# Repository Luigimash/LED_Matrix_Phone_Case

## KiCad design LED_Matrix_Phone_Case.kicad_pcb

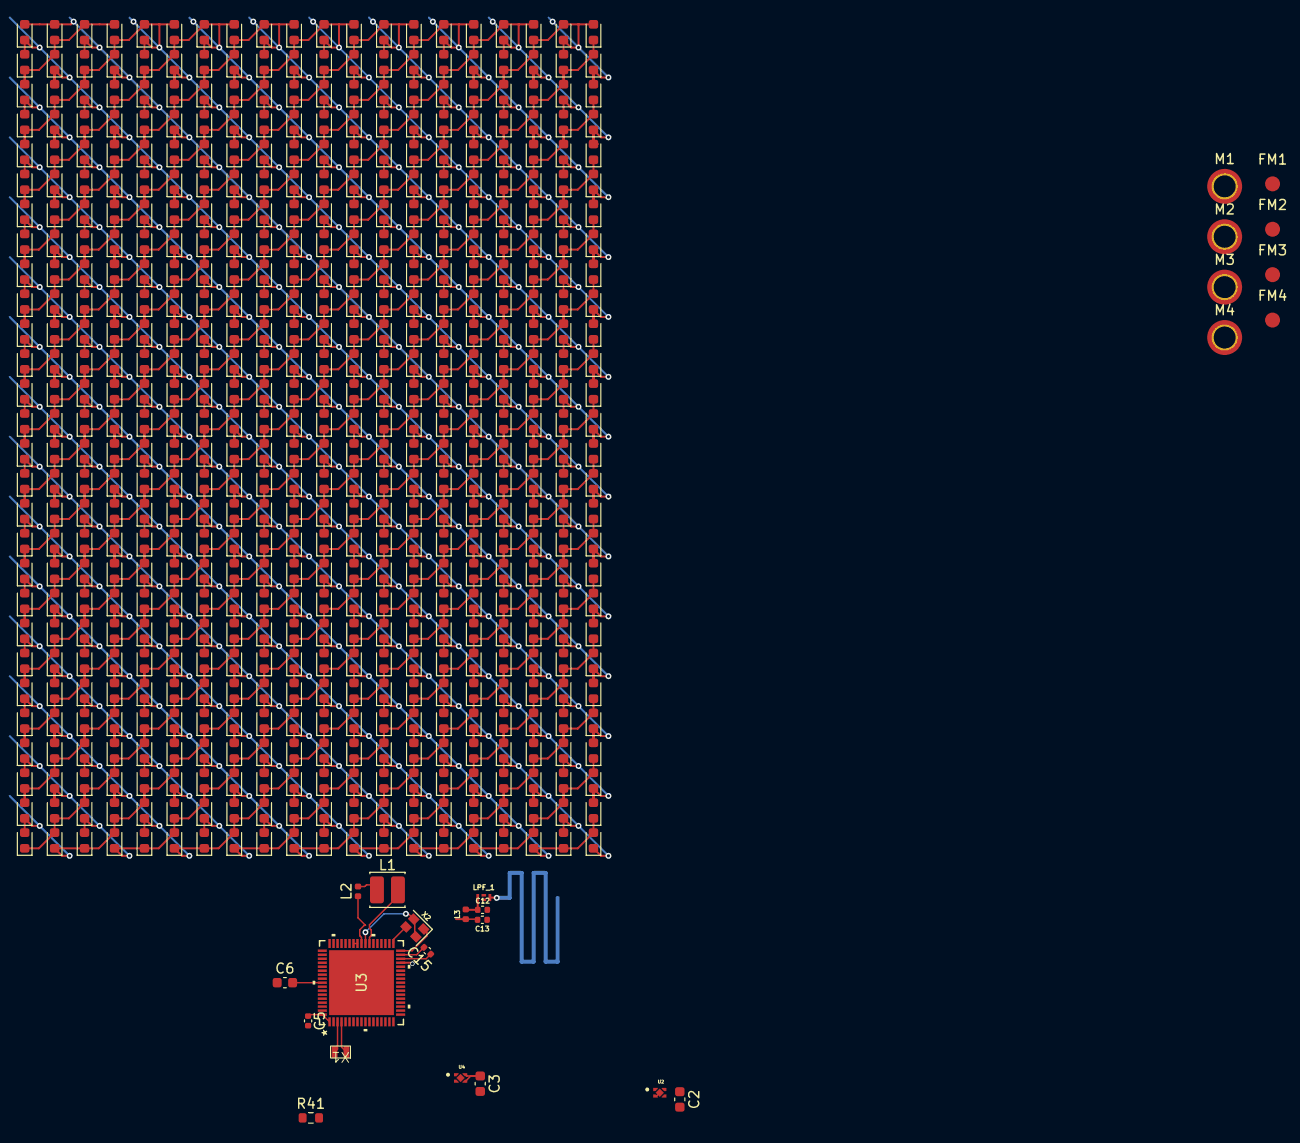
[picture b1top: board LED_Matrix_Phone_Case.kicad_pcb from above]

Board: 2 copper layers, 25 parts (0 on the bottom side), 14 nets.

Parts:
C2, C3: 4.7uF; C_0603_1608Metric
C5, C15: 100nF; C_0402_1005Metric
C6: 4.7µF; C_0603_1608Metric
C12: 0.3pF; C_0402_1005Metric
C13: 0.8pF; C_0402_1005Metric
FM1, FM2, FM3, FM4: Fiducial; Fiducial_1.5mm_Mask3mm
L1: 10uH; L_Cenker_CKCS3015
L2: 10nH; L_0402_1005Metric
L3: 2.7nH; L_0402_1005Metric
LPF_1: DLF162500LT-5028A1 - Low Pass Filter; DLF-4_1P6X0P8
M1, M2, M3, M4: MountingHole_Pad; MountingHole_2.2mm_M2_ISO7380_Pad_TopBottom
R41: 5.1kΩ; R_0603_1608Metric
U2: TPS7A0233PDQNR_PHONE; IC_TPS7A0233PDQNR
U3: STM32WB55RGV6; VFQFN68-8x8mm
U4: TPS7A0233PDQNR_PC; IC_TPS7A0233PDQNR
X1: 32.768KHz; SMD1610
X2: 32MHz; Crystal_SMD_2016-4Pin_2.0x1.6mm

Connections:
/3.3V_PC: C6.2, U3.60 (PC12), U4.1 (OUT)
/3.3V_PHONE: C5.1, C15.2, U2.1 (OUT), U3.1 (VBAT), U3.14 (VDDA), U3.30 (VDD), U3.33 (VDDRF), U3.44 (VDDSMPS), U3.45 (VDD), U3.55 (VDDUSB), U3.68 (VDD)
/HSE_IN: U3.35 (OSC_IN), X2.3
/HSE_OUT: U3.34 (OSC_OUT), X2.1
/LSE_IN: U3.3 (PC14-OSC32_IN), X1.2
/LSE_OUT: U3.4 (PC15-OSC32_OUT), X1.1
/Matching_Network: C12.1, L3.2, LPF_1.1 (IN)
/RF1: C13.1, L3.1, U3.31 (RF1)
/SMPSFB: L1.2, U3.41 (VFBSMPS)
/SMPSLX: L2.1, U3.43 (VLXSMPS)
/SMPSLXL: L1.1, L2.2
/USB_F_IN_5V: C3.1, U4.3 (EN), U4.4 (IN)
/USB_M_IN_5V: C2.1, U2.3 (EN), U2.4 (IN)
GND: C2.2, C3.2, C5.2, C6.1, C12.2, C13.2, C15.1, LPF_1.2 (GND), LPF_1.4 (GND), M1.1, M2.1, M3.1, M4.1, R41.2, U2.2 (GND), U2.5 (THERMAL_PAD), U3.8 (NRST), U3.32 (VSSRF), U3.42 (VSSSMPS), U3.69 (EPAD), U4.2 (GND), U4.5 (THERMAL_PAD), X2.2, X2.4

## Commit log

2025-10-10 init commit
2025-11-08 ver 1.1 files, i fucked up the flex board to main board pads on v1.0 but fixed in 1.1
2025-11-08 adding some media
2025-11-09 generating pin-pixel mapping
2025-11-09 mkdir pin_pixel_mapping
2025-11-13 added stm32 generated code
2025-11-13 thinking
2025-11-13 CLI image to ASCII PGM conversion
2025-11-13 changing output folder location
2025-11-13 gitignoring
